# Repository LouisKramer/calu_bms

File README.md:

# calu_bms

Battery management system for a stationary high-voltage LFP home storage
(8 × 16S modules, expandable to 10, wireless slaves, master with CAN to the inverter).

Development follows the documents in [docs/](docs/):

1. [System requirements](docs/requirements.md) (draft, incl. configuration parameters)
2. [Slave requirements](docs/slave_requirements.md) (draft, hardware + software)
3. [Master requirements](docs/master_requirements.md) (draft, hardware + software), based on the
   [master concept review](docs/master_concept_review.md) of `hw/master/CALU_BMS_MASTER.epro2`
4. [Plausibility check](docs/plausibility_check.md) of the requirements
5. [System architecture](docs/system_architecture.md), [master architecture](docs/master_architecture.md), [slave architecture](docs/slave_architecture.md)
6. [Project plan](docs/plan.md) with work items ([tools/work_items.json](tools/work_items.json), GitHub issues via [tools/create_github_issues.py](tools/create_github_issues.py))

## Repository layout

| Folder | Content |
|---|---|
| [docs/](docs/) | requirements, plausibility check, architecture, plan, datasheets, test reports |
| [firmware/](firmware/) | MicroPython firmware: `common/`, `slave/`, `master/`, `build/` |
| [hw/](hw/) | hardware: `slave/`, `master/` |
| [tools/](tools/) | helper scripts (work items, later CAN sniffer, calibration, production test) |
| [tests/](tests/) | host tests (CPython + pytest) with simulated hardware |

## Development

```
pip install -r requirements-dev.txt
pytest
```

Work items are GitHub issues (milestones M0…M3). Each work item gets a branch (`w01-repo-skeleton`)
and a pull request that references the issue (`Closes #2`).

## Earlier work

The `playground` branch (formerly `main`) holds the first prototypes, firmware and hardware.
It is kept as a reference only, together with these branches:

| Branch | Content |
|---|---|
| `playground` | first master/slave firmware (MicroPython), EasyEDA hardware 1.2/1.3, tools, datasheets |
| `slave-hw-2.0.1.0` | firmware cleanup, drivers and bring-up for slave hardware 2.0.1.0 |
| `slave-hw-3.0.0.0` | flying-capacitor slave in KiCad/SKiDL, active balancer review |

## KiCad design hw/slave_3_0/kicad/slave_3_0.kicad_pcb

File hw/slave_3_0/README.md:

# Slave 3.0.0.0 hardware (KiCad 10 + SKiDL)

The circuit is written in Python (SKiDL). Everything in `kicad/` except the PCB layout is generated.

| File | Content |
|---|---|
| `common.py` | KiCad paths, part helpers, reference numbering (one hundred block per sheet), shared nets |
| `power.py`, `mcu.py`, `cells.py`, `meas_mux.py`, `adc.py`, `balancing.py` | one schematic sheet each |
| `slave_3_0.py` | top level: ERC, netlist, schematic, checks, `--pcb` |
| `sch_writer.py` | writes the KiCad schematic (symbols + global labels) and the project file, verifies it |
| `build_pcb.py` | creates the initial PCB (only if none exists) |
| `kicad/` | generated KiCad project: open `slave_3_0.kicad_pro` |

Specification and design reasoning: [../CALU_BMS_Slave_3_0_0_0_schematic.md](../CALU_BMS_Slave_3_0_0_0_schematic.md)

## Workflow

```
make hw_tools   # once: SKiDL into KiCad's Python
make sch        # edit *.py, then regenerate netlist + schematic (verified against the netlist)
make erc        # KiCad ERC
make pcb        # first time only: initial PCB with all footprints, nets and net classes
make drc        # KiCad DRC incl. schematic <-> PCB parity
```

After a circuit change: `make sch`, then in KiCad **reload the schematic** (schematic editor: File → Revert, or
close it), then in the PCB editor **Tools → Update PCB from Schematic (F8)** and save (Ctrl+S).
F8 uses the schematic editor's data in memory: without the reload it applies the old circuit.
Footprints stay linked to their symbols (deterministic UUIDs), so the layout is kept.

Do not edit the generated `.kicad_sch` files in KiCad; change the Python source instead.
The PCB (`slave_3_0.kicad_pcb`) is edited in KiCad as usual.

## Schematic style

No wires: every pin has a global label with its net name. Unnamed nets are called `N$<n>`.
`make sch` exports KiCad's netlist of the generated schematic and compares it pin by pin with the SKiDL
netlist, so the drawing can't differ from the circuit.

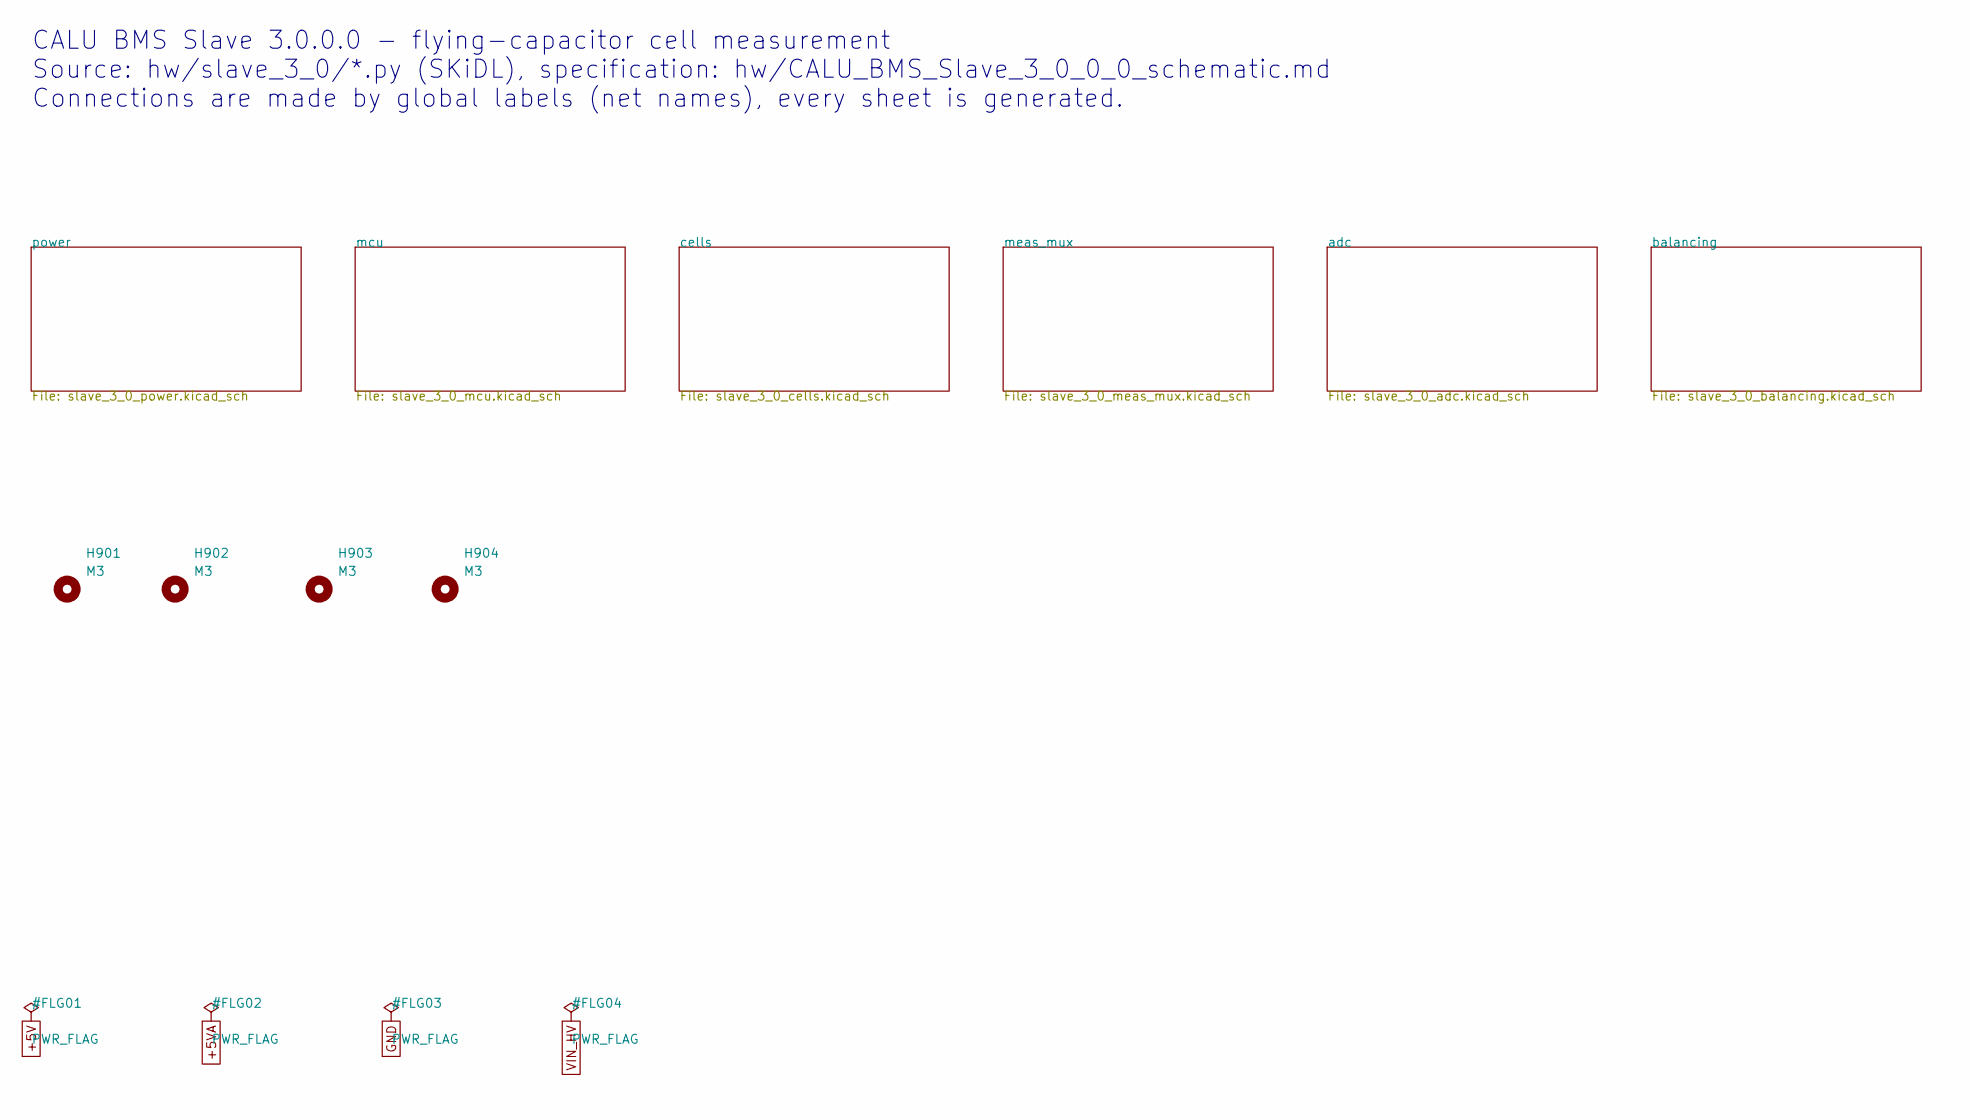
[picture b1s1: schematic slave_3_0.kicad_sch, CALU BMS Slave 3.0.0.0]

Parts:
H901, H902, H903, H904: M3; MountingHole_3.2mm_M3

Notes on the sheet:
CALU BMS Slave 3.0.0.0 - flying-capacitor cell measurement Source: hw/slave_3_0/*.py (SKiDL), specification: hw/CALU_BMS_Slave_3_0_0_0_schematic.md Connections are made by global labels (net names), every sheet is generated.

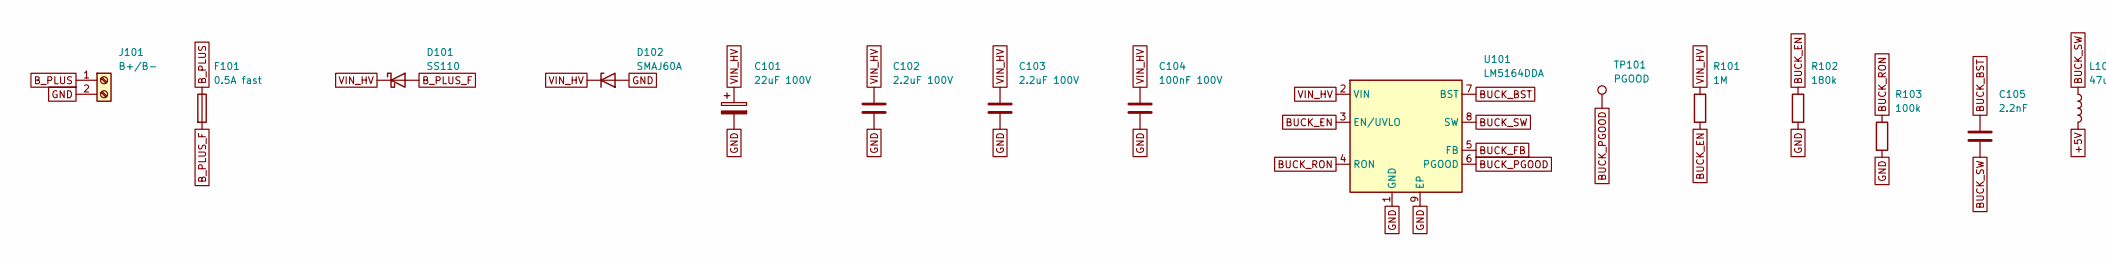
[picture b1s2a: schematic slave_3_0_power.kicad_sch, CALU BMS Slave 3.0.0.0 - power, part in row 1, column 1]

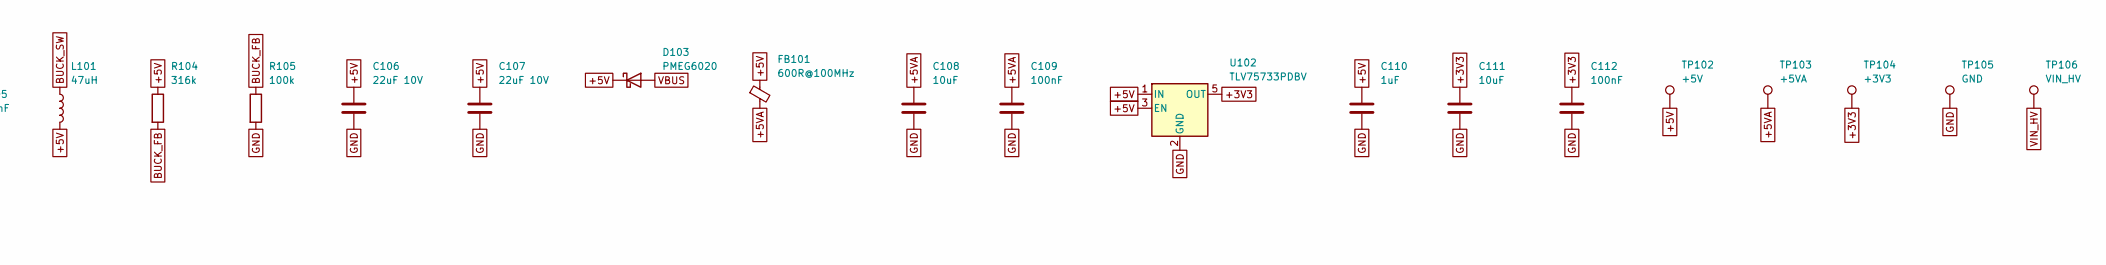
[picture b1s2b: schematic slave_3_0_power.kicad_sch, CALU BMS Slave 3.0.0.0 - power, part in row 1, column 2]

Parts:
C101: 22uF 100V; CP_Elec_8x10
C102, C103: 2.2uF 100V; C_1210_3225Metric
C104: 100nF 100V; C_0603_1608Metric
C105: 2.2nF; C_0603_1608Metric
C106, C107: 22uF 10V; C_1206_3216Metric
C108, C111: 10uF; C_0603_1608Metric
C109, C112: 100nF; C_0603_1608Metric
C110: 1uF; C_0603_1608Metric
D101: SS110; D_SMA
D102: SMAJ60A; D_SMA
D103: PMEG6020; D_SOD-123F
F101: 0.5A fast; Fuse_1206_3216Metric
FB101: 600R@100MHz; L_0603_1608Metric
J101: B+/B-; PhoenixContact_MSTBA_2,5_2-G-5,08_1x02_P5.08mm_Horizontal
L101: 47uH; L_Bourns_SRR1260
R101: 1M; R_0805_2012Metric
R102: 180k; R_0603_1608Metric
R103, R105: 100k; R_0603_1608Metric
R104: 316k; R_0603_1608Metric
TP101: PGOOD; TestPoint_Pad_D1.0mm
TP102: +5V; TestPoint_Pad_D1.0mm
TP103: +5VA; TestPoint_Pad_D1.0mm
TP104: +3V3; TestPoint_Pad_D1.0mm
TP105: GND; TestPoint_Pad_D1.0mm
TP106: VIN_HV; TestPoint_Pad_D1.0mm
U101: LM5164DDA; HSOP-8-1EP_3.9x4.9mm_P1.27mm_EP2.41x3.1mm_ThermalVias
U102: TLV75733PDBV; SOT-23-5

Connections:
+3V3: C111.1, C112.1, TP104.1 (1_1), U102.5 (OUT); also elsewhere on the board
+5V: C106.1, C107.1, C110.1, D103.1 (K), FB101.1, L101.2, R104.1, TP102.1 (1_1), U102.1 (IN), U102.3 (EN); also elsewhere on the board
+5VA: C108.1, C109.1, FB101.2, TP103.1 (1_1); also elsewhere on the board
BUCK_BST: C105.1, U101.7 (BST)
BUCK_EN: R101.2, R102.1, U101.3 (EN/UVLO)
BUCK_FB: R104.2, R105.1, U101.5 (FB)
BUCK_PGOOD: TP101.1 (1_1), U101.6 (PGOOD)
BUCK_RON: R103.1, U101.4 (RON)
BUCK_SW: C105.2, L101.1, U101.8 (SW)
B_PLUS: F101.1, J101.1
B_PLUS_F: D101.2 (A), F101.2
GND: C101.2, C102.2, C103.2, C104.2, C106.2, C107.2, C108.2, C109.2, C110.2, C111.2, C112.2, D102.2 (A), J101.2, R102.2, R103.2, R105.2, TP105.1 (1_1), U101.1 (GND), U101.9 (EP), U102.2 (GND); also elsewhere on the board
VBUS: D103.2 (A); also elsewhere on the board
VIN_HV: C101.1, C102.1, C103.1, C104.1, D101.1 (K), D102.1 (K), R101.1, TP106.1 (1_1), U101.2 (VIN)

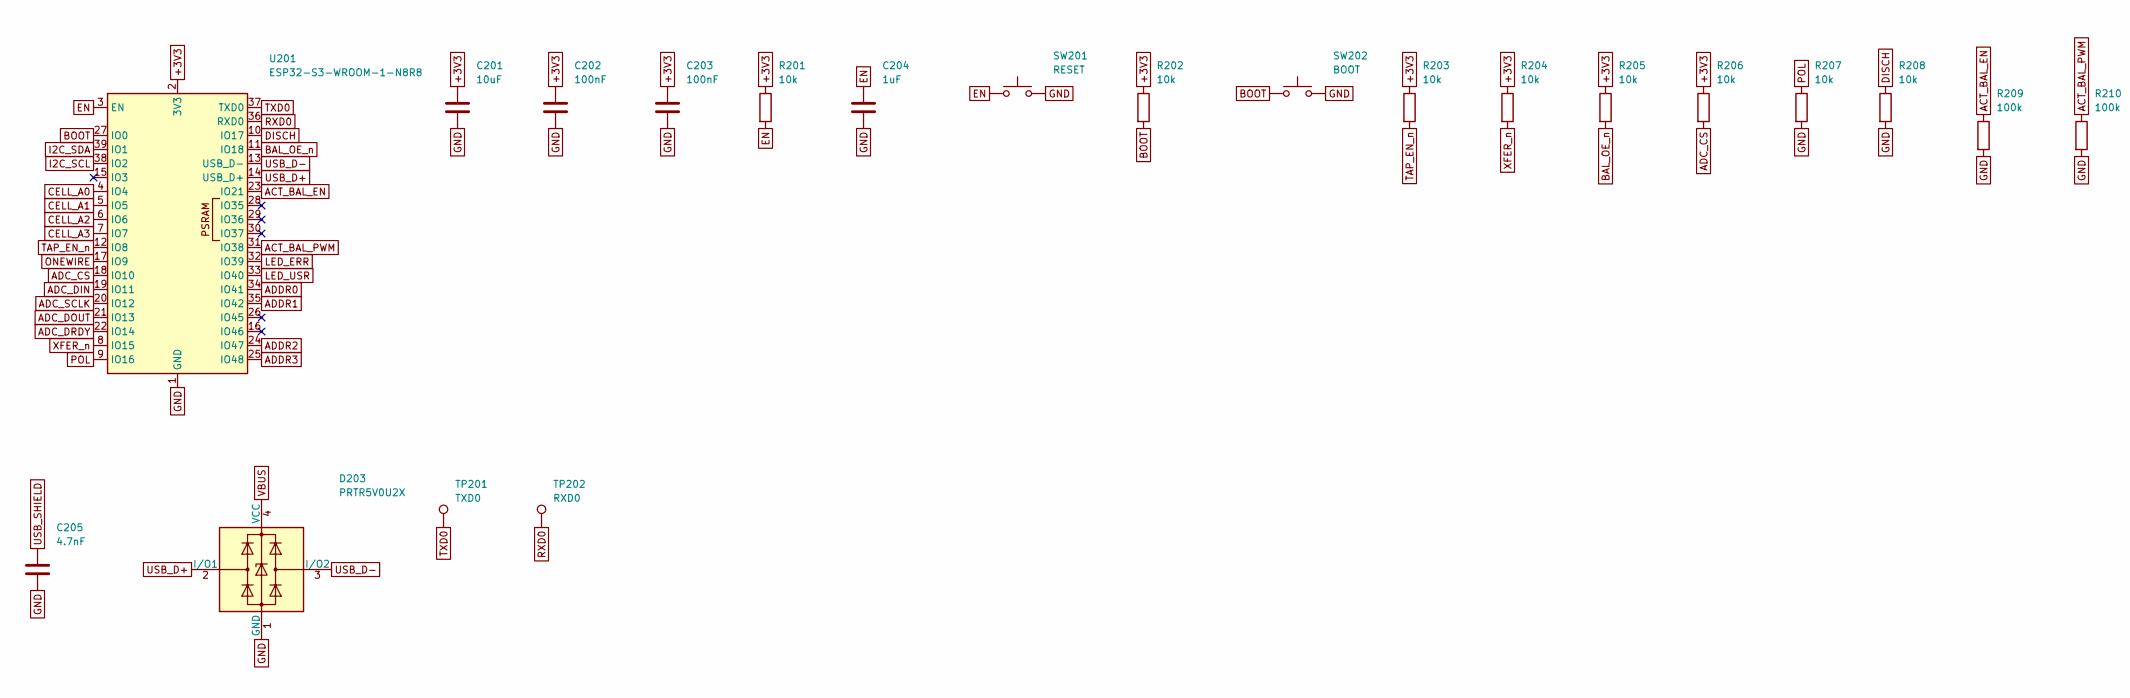
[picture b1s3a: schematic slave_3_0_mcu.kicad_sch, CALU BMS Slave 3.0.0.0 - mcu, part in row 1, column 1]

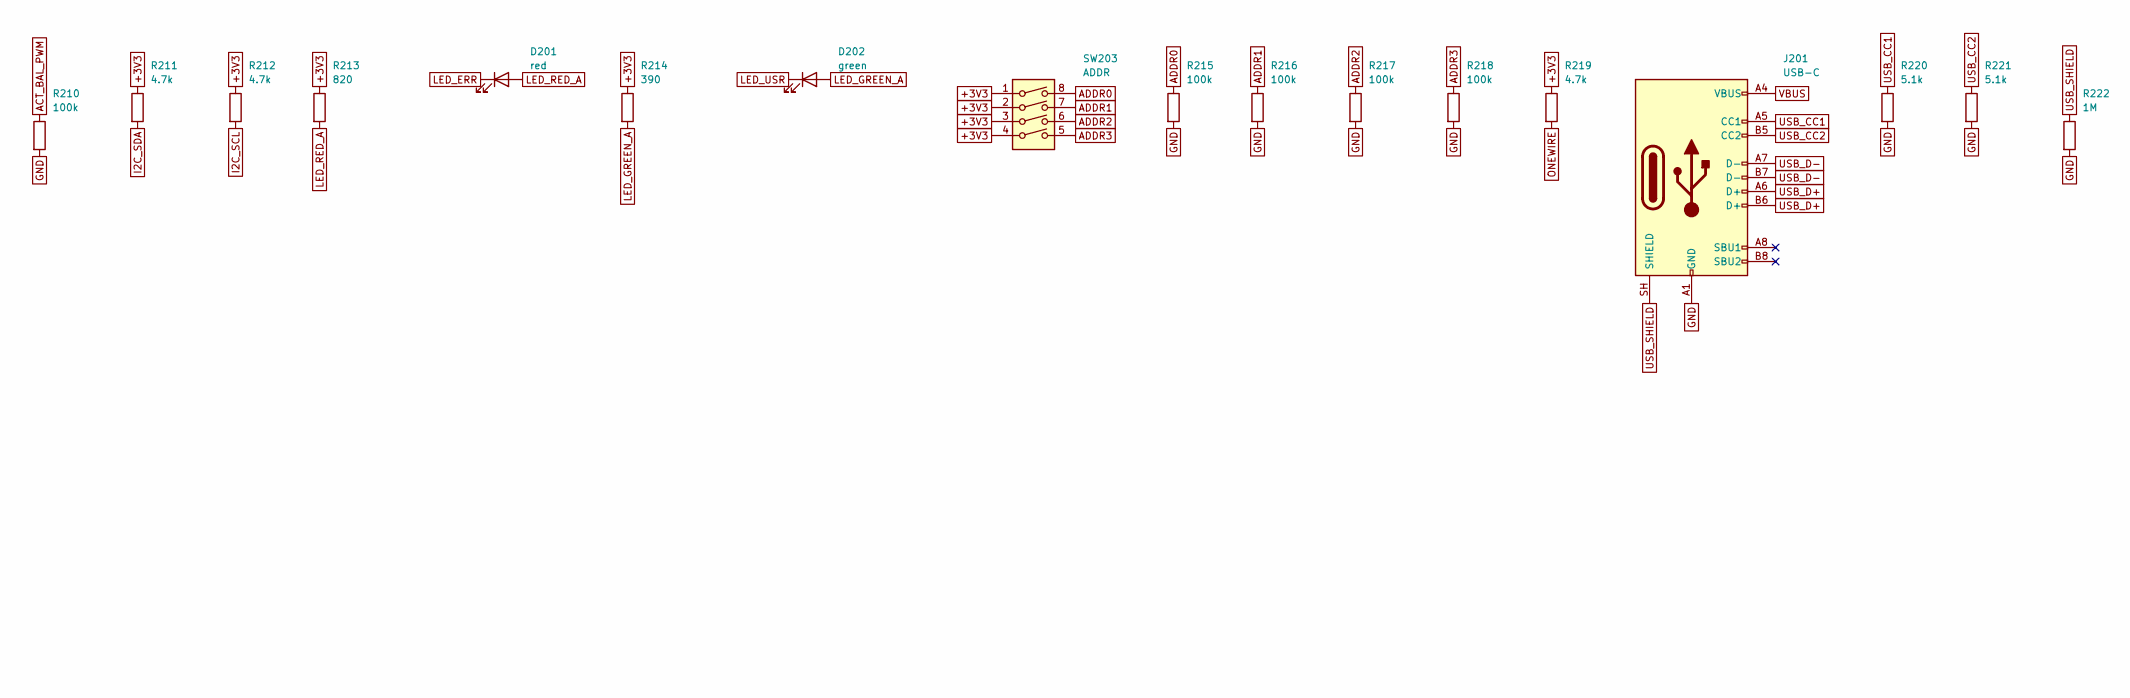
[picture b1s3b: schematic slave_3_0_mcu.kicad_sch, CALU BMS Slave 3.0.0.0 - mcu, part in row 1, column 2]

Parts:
C201: 10uF; C_0603_1608Metric
C202, C203: 100nF; C_0603_1608Metric
C204: 1uF; C_0603_1608Metric
C205: 4.7nF; C_0603_1608Metric
D201: red; LED_0603_1608Metric
D202: green; LED_0603_1608Metric
D203: PRTR5V0U2X; SOT-143
J201: USB-C; USB_C_Receptacle_HRO_TYPE-C-31-M-12
R201, R202, R203, R204, R205, R206, R207, R208: 10k; R_0603_1608Metric
R209, R210, R215, R216, R217, R218: 100k; R_0603_1608Metric
R211, R212, R219: 4.7k; R_0603_1608Metric
R213: 820; R_0603_1608Metric
R214: 390; R_0603_1608Metric
R220, R221: 5.1k; R_0603_1608Metric
R222: 1M; R_0603_1608Metric
SW201: RESET; SW_SPST_B3U-1000P
SW202: BOOT; SW_SPST_B3U-1000P
SW203: ADDR; SW_DIP_SPSTx04_Slide_9.78x12.34mm_W7.62mm_P2.54mm
TP201: TXD0; TestPoint_Pad_D1.0mm
TP202: RXD0; TestPoint_Pad_D1.0mm
U201: ESP32-S3-WROOM-1-N8R8; ESP32-S3-WROOM-1

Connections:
+3V3: C201.1, C202.1, C203.1, R201.1, R202.1, R203.1, R204.1, R205.1, R206.1, R211.1, R212.1, R213.1, R214.1, R219.1, SW203.1, SW203.2, SW203.3, SW203.4, U201.2 (3V3); also elsewhere on the board
ACT_BAL_EN: R209.1, U201.23 (IO21); also elsewhere on the board
ACT_BAL_PWM: R210.1, U201.31 (IO38); also elsewhere on the board
ADC_CS: R206.2, U201.18 (IO10); also elsewhere on the board
ADC_DIN: U201.19 (IO11); also elsewhere on the board
ADC_DOUT: U201.21 (IO13); also elsewhere on the board
ADC_DRDY: U201.22 (IO14); also elsewhere on the board
ADC_SCLK: U201.20 (IO12); also elsewhere on the board
ADDR0: R215.1, SW203.8, U201.34 (IO41)
ADDR1: R216.1, SW203.7, U201.35 (IO42)
ADDR2: R217.1, SW203.6, U201.24 (IO47)
ADDR3: R218.1, SW203.5, U201.25 (IO48)
BAL_OE_n: R205.2, U201.11 (IO18); also elsewhere on the board
BOOT: R202.2, SW202.1, U201.27 (IO0)
CELL_A0: U201.4 (IO4); also elsewhere on the board
CELL_A1: U201.5 (IO5); also elsewhere on the board
CELL_A2: U201.6 (IO6); also elsewhere on the board
CELL_A3: U201.7 (IO7); also elsewhere on the board
DISCH: R208.1, U201.10 (IO17); also elsewhere on the board
EN: C204.1, R201.2, SW201.1, U201.3 (EN)
GND: C201.2, C202.2, C203.2, C204.2, C205.2, D203.1 (GND), J201.A1 (GND), J201.A12 (GND), J201.B1 (GND), J201.B12 (GND), R207.2, R208.2, R209.2, R210.2, R215.2, R216.2, R217.2, R218.2, R220.2, R221.2, R222.2, SW201.2, SW202.2, U201.1 (GND), U201.40 (GND), U201.41 (GND); also elsewhere on the board
I2C_SCL: R212.2, U201.38 (IO2); also elsewhere on the board
I2C_SDA: R211.2, U201.39 (IO1); also elsewhere on the board
LED_ERR: D201.1 (K), U201.32 (IO39)
LED_GREEN_A: D202.2 (A), R214.2
LED_RED_A: D201.2 (A), R213.2
LED_USR: D202.1 (K), U201.33 (IO40)
ONEWIRE: R219.2, U201.17 (IO9); also elsewhere on the board
POL: R207.1, U201.9 (IO16); also elsewhere on the board
RXD0: TP202.1 (1_1), U201.36 (RXD0)
TAP_EN_n: R203.2, U201.12 (IO8); also elsewhere on the board
TXD0: TP201.1 (1_1), U201.37 (TXD0)
USB_CC1: J201.A5 (CC1), R220.1
USB_CC2: J201.B5 (CC2), R221.1
USB_D+: D203.2 (I/O1), J201.A6 (D+), J201.B6 (D+), U201.14 (USB_D+)
USB_D-: D203.3 (I/O2), J201.A7 (D-), J201.B7 (D-), U201.13 (USB_D-)
USB_SHIELD: C205.1, J201.SH (SHIELD), R222.1
VBUS: D203.4 (VCC), J201.A4 (VBUS), J201.A9 (VBUS), J201.B4 (VBUS), J201.B9 (VBUS); also elsewhere on the board
XFER_n: R204.2, U201.8 (IO15); also elsewhere on the board

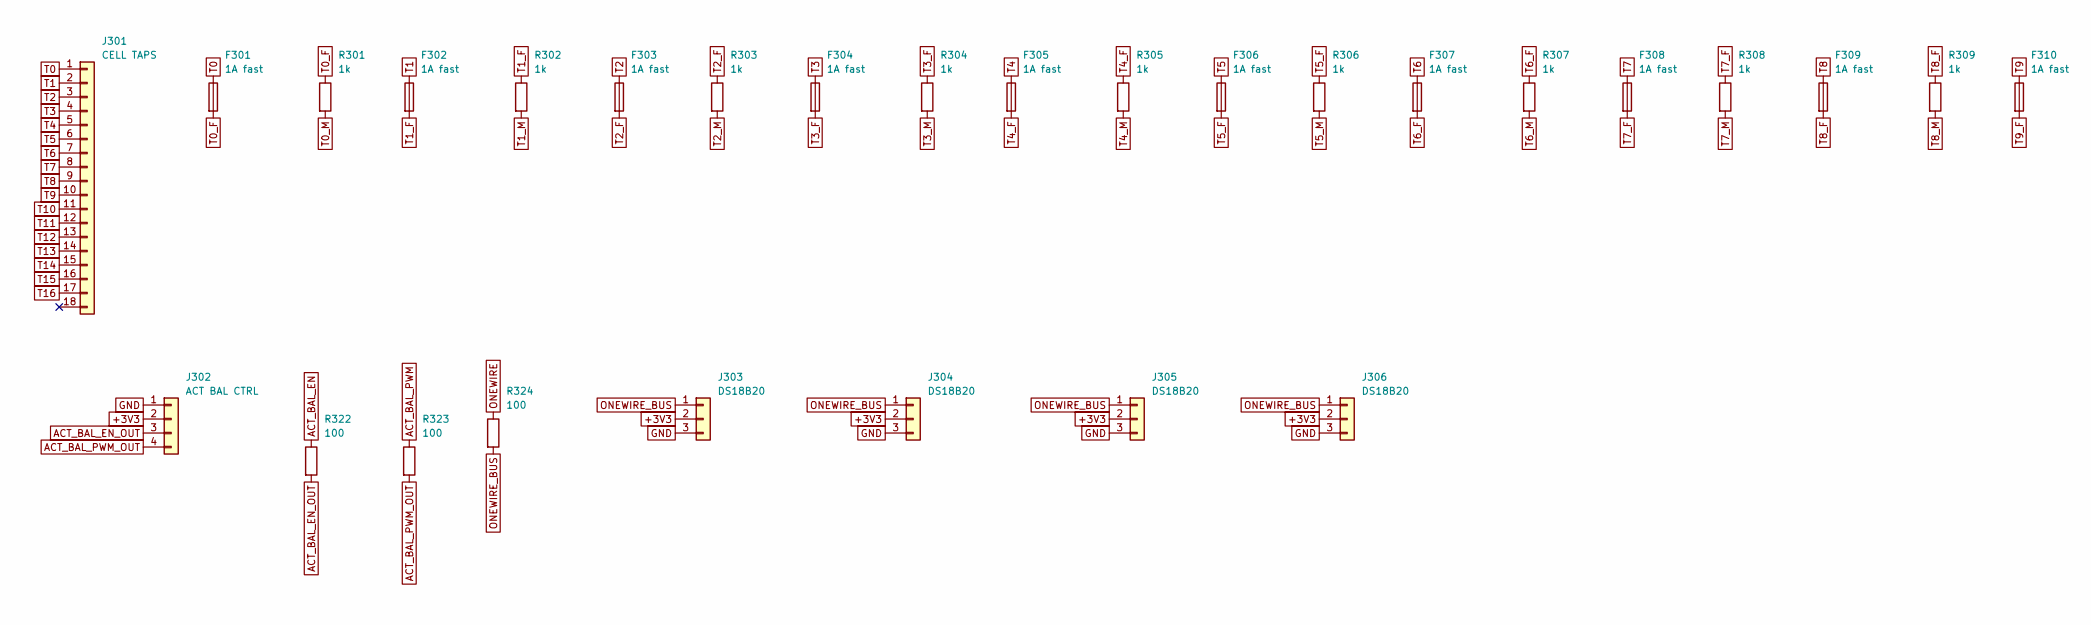
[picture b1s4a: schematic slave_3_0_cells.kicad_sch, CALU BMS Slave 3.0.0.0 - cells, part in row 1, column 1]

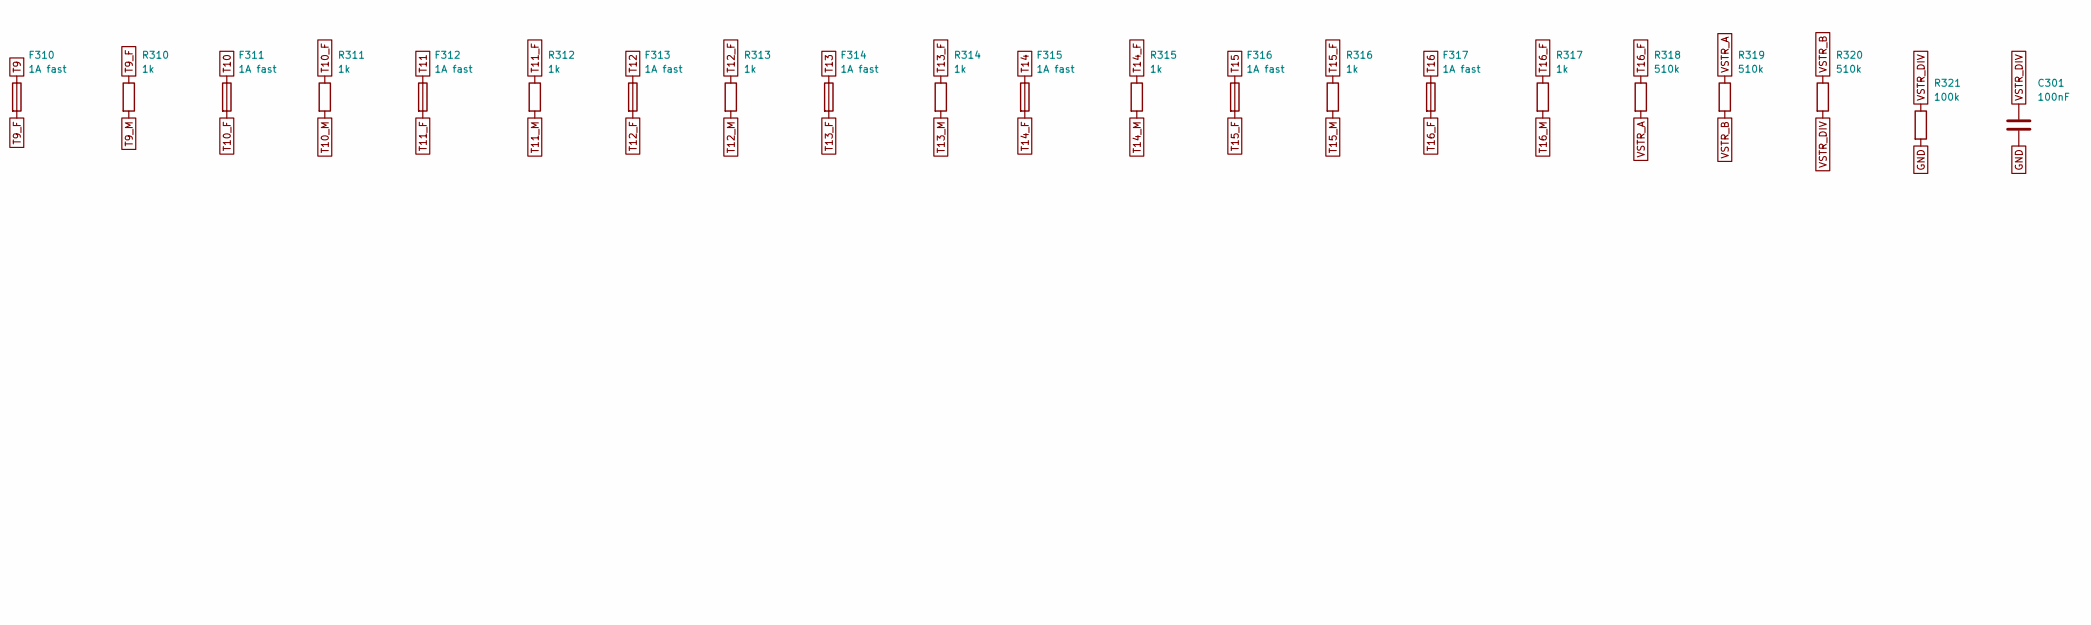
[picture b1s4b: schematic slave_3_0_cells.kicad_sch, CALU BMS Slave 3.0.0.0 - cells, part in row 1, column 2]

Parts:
C301: 100nF; C_0603_1608Metric
F301, F302, F303, F304, F305, F306, F307, F308, F309, F310, F311, F312, F313, F314, F315, F316, F317: 1A fast; Fuse_1206_3216Metric
J301: CELL TAPS; TerminalBlock_Degson_DG250-3.5-18P_1x18_P3.50mm_45Degree
J302: ACT BAL CTRL; JST_XH_B4B-XH-A_1x04_P2.50mm_Vertical
J303, J304, J305, J306: DS18B20; TerminalBlock_Degson_DG250-3.5-03P_1x03_P3.50mm_45Degree
R301, R302, R303, R304, R305, R306, R307, R308, R309, R310, R311, R312, R313, R314, R315, R316, R317: 1k; R_1206_3216Metric
R318, R319, R320: 510k; R_0805_2012Metric
R321: 100k; R_0603_1608Metric
R322, R323, R324: 100; R_0603_1608Metric

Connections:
+3V3: J302.2, J303.2, J304.2, J305.2, J306.2; also elsewhere on the board
ACT_BAL_EN: R322.1; also elsewhere on the board
ACT_BAL_EN_OUT: J302.3, R322.2
ACT_BAL_PWM: R323.1; also elsewhere on the board
ACT_BAL_PWM_OUT: J302.4, R323.2
GND: C301.2, J302.1, J303.3, J304.3, J305.3, J306.3, R321.2; also elsewhere on the board
ONEWIRE: R324.1; also elsewhere on the board
ONEWIRE_BUS: J303.1, J304.1, J305.1, J306.1, R324.2
T0: F301.1, J301.1
T0_F: F301.2, R301.1; also elsewhere on the board
T0_M: R301.2; also elsewhere on the board
T1: F302.1, J301.2
T1_F: F302.2, R302.1; also elsewhere on the board
T1_M: R302.2; also elsewhere on the board
T2: F303.1, J301.3
T2_F: F303.2, R303.1; also elsewhere on the board
T2_M: R303.2; also elsewhere on the board
T3: F304.1, J301.4
T3_F: F304.2, R304.1; also elsewhere on the board
T3_M: R304.2; also elsewhere on the board
T4: F305.1, J301.5
T4_F: F305.2, R305.1; also elsewhere on the board
T4_M: R305.2; also elsewhere on the board
T5: F306.1, J301.6
T5_F: F306.2, R306.1; also elsewhere on the board
T5_M: R306.2; also elsewhere on the board
T6: F307.1, J301.7
T6_F: F307.2, R307.1; also elsewhere on the board
T6_M: R307.2; also elsewhere on the board
T7: F308.1, J301.8
T7_F: F308.2, R308.1; also elsewhere on the board
T7_M: R308.2; also elsewhere on the board
T8: F309.1, J301.9
T8_F: F309.2, R309.1; also elsewhere on the board
T8_M: R309.2; also elsewhere on the board
T9: F310.1, J301.10
T9_F: F310.2, R310.1; also elsewhere on the board
T9_M: R310.2; also elsewhere on the board
T10: F311.1, J301.11
T10_F: F311.2, R311.1; also elsewhere on the board
T10_M: R311.2; also elsewhere on the board
T11: F312.1, J301.12
T11_F: F312.2, R312.1; also elsewhere on the board
T11_M: R312.2; also elsewhere on the board
T12: F313.1, J301.13
T12_F: F313.2, R313.1; also elsewhere on the board
T12_M: R313.2; also elsewhere on the board
T13: F314.1, J301.14
T13_F: F314.2, R314.1; also elsewhere on the board
T13_M: R314.2; also elsewhere on the board
T14: F315.1, J301.15
T14_F: F315.2, R315.1; also elsewhere on the board
T14_M: R315.2; also elsewhere on the board
T15: F316.1, J301.16
T15_F: F316.2, R316.1; also elsewhere on the board
T15_M: R316.2; also elsewhere on the board
T16: F317.1, J301.17
T16_F: F317.2, R317.1, R318.1; also elsewhere on the board
T16_M: R317.2; also elsewhere on the board
VSTR_A: R318.2, R319.1
VSTR_B: R319.2, R320.1
VSTR_DIV: C301.1, R320.2, R321.1; also elsewhere on the board

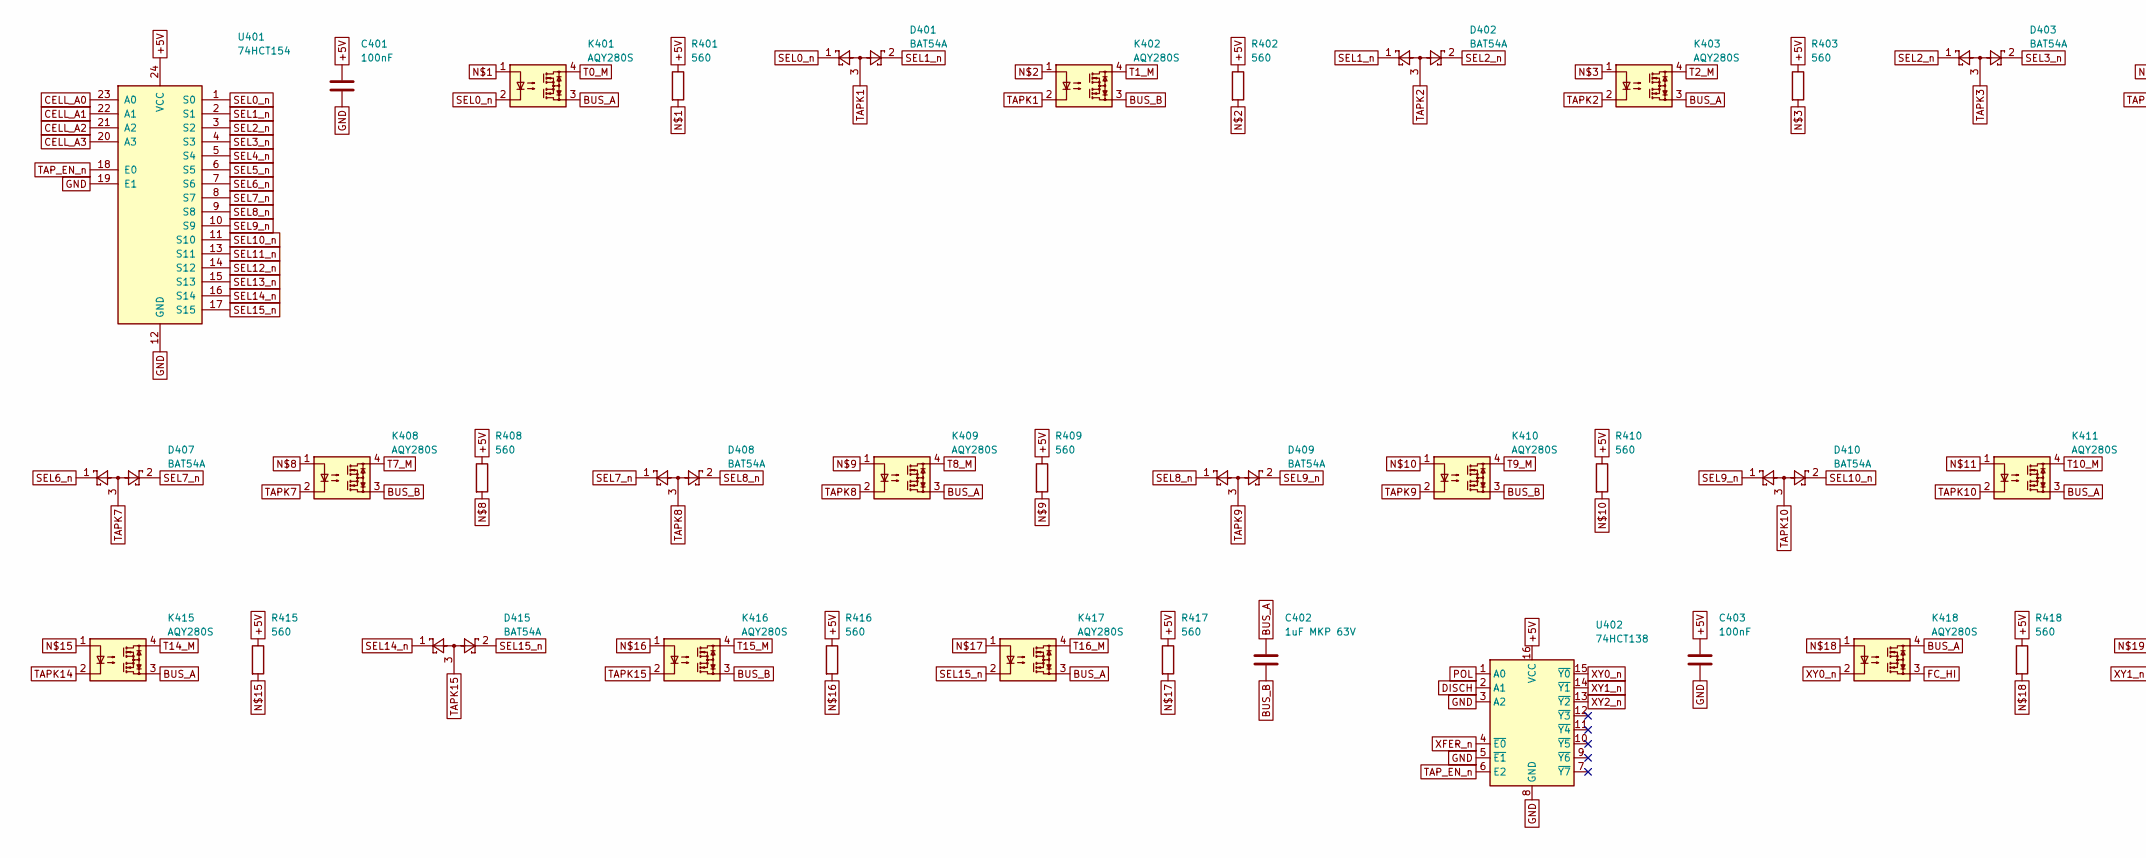
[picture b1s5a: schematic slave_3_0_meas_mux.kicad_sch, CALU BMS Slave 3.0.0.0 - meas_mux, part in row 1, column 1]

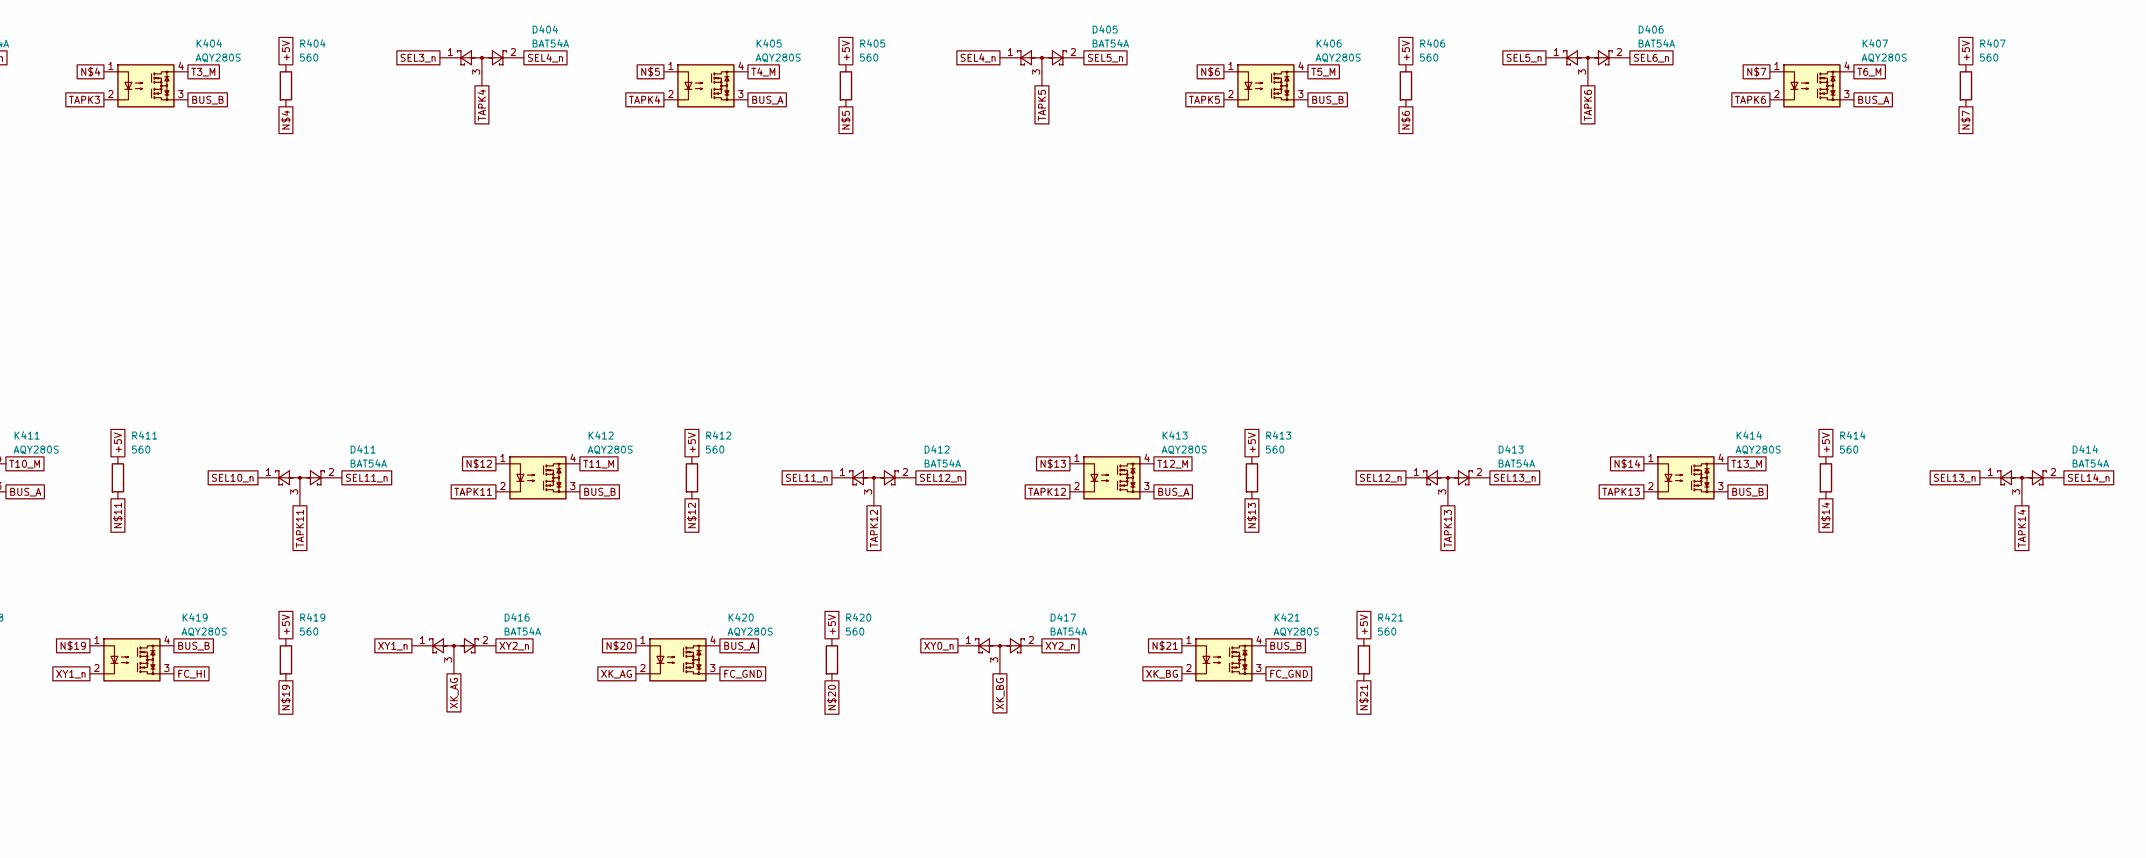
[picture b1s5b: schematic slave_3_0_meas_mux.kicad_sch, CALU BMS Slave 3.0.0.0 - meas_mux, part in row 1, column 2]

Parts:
C401, C403: 100nF; C_0603_1608Metric
C402: 1uF MKP 63V; C_Rect_L13.0mm_W5.0mm_P10.00mm_FKS3_FKP3_MKS4
D401, D402, D403, D404, D405, D406, D407, D408, D409, D410, D411, D412, D413, D414, D415, D416, D417: BAT54A; SOT-23
K401, K402, K403, K404, K405, K406, K407, K408, K409, K410, K411, K412, K413, K414, K415, K416, K417, K418, K419, K420, K421: AQY280S; SO-4_4.4x3.9mm_P2.54mm
R401, R402, R403, R404, R405, R406, R407, R408, R409, R410, R411, R412, R413, R414, R415, R416, R417, R418, R419, R420, R421: 560; R_0603_1608Metric
U401: 74HCT154; SOIC-24W_7.5x15.4mm_P1.27mm
U402: 74HCT138; SOIC-16_3.9x9.9mm_P1.27mm

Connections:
+5V: C401.1, C403.1, R401.1, R402.1, R403.1, R404.1, R405.1, R406.1, R407.1, R408.1, R409.1, R410.1, R411.1, R412.1, R413.1, R414.1, R415.1, R416.1, R417.1, R418.1, R419.1, R420.1, R421.1, U401.24 (VCC), U402.16 (VCC); also elsewhere on the board
BUS_A: C402.1, K401.3, K403.3, K405.3, K407.3, K409.3, K411.3, K413.3, K415.3, K417.3, K418.4, K420.4
BUS_B: C402.2, K402.3, K404.3, K406.3, K408.3, K410.3, K412.3, K414.3, K416.3, K419.4, K421.4
CELL_A0: U401.23 (A0); also elsewhere on the board
CELL_A1: U401.22 (A1); also elsewhere on the board
CELL_A2: U401.21 (A2); also elsewhere on the board
CELL_A3: U401.20 (A3); also elsewhere on the board
DISCH: U402.2 (A1); also elsewhere on the board
FC_GND: K420.3, K421.3; also elsewhere on the board
FC_HI: K418.3, K419.3; also elsewhere on the board
GND: C401.2, C403.2, U401.12 (GND), U401.19 (E1), U402.3 (A2), U402.5 (~E1), U402.8 (GND); also elsewhere on the board
unnamed: K401.1, R401.2
unnamed: K402.1, R402.2
unnamed: K403.1, R403.2
unnamed: K404.1, R404.2
unnamed: K405.1, R405.2
unnamed: K406.1, R406.2
unnamed: K407.1, R407.2
unnamed: K408.1, R408.2
unnamed: K409.1, R409.2
unnamed: K410.1, R410.2
unnamed: K411.1, R411.2
unnamed: K412.1, R412.2
unnamed: K413.1, R413.2
unnamed: K414.1, R414.2
unnamed: K415.1, R415.2
unnamed: K416.1, R416.2
unnamed: K417.1, R417.2
unnamed: K418.1, R418.2
unnamed: K419.1, R419.2
unnamed: K420.1, R420.2
unnamed: K421.1, R421.2
POL: U402.1 (A0); also elsewhere on the board
SEL0_n: D401.1, K401.2, U401.1 (S0)
SEL1_n: D401.2, D402.1, U401.2 (S1)
SEL2_n: D402.2, D403.1, U401.3 (S2)
SEL3_n: D403.2, D404.1, U401.4 (S3)
SEL4_n: D404.2, D405.1, U401.5 (S4)
SEL5_n: D405.2, D406.1, U401.6 (S5)
SEL6_n: D406.2, D407.1, U401.7 (S6)
SEL7_n: D407.2, D408.1, U401.8 (S7)
SEL8_n: D408.2, D409.1, U401.9 (S8)
SEL9_n: D409.2, D410.1, U401.10 (S9)
SEL10_n: D410.2, D411.1, U401.11 (S10)
SEL11_n: D411.2, D412.1, U401.13 (S11)
SEL12_n: D412.2, D413.1, U401.14 (S12)
SEL13_n: D413.2, D414.1, U401.15 (S13)
SEL14_n: D414.2, D415.1, U401.16 (S14)
SEL15_n: D415.2, K417.2, U401.17 (S15)
T0_M: K401.4; also elsewhere on the board
T1_M: K402.4; also elsewhere on the board
T2_M: K403.4; also elsewhere on the board
T3_M: K404.4; also elsewhere on the board
T4_M: K405.4; also elsewhere on the board
T5_M: K406.4; also elsewhere on the board
T6_M: K407.4; also elsewhere on the board
T7_M: K408.4; also elsewhere on the board
T8_M: K409.4; also elsewhere on the board
T9_M: K410.4; also elsewhere on the board
T10_M: K411.4; also elsewhere on the board
T11_M: K412.4; also elsewhere on the board
T12_M: K413.4; also elsewhere on the board
T13_M: K414.4; also elsewhere on the board
T14_M: K415.4; also elsewhere on the board
T15_M: K416.4; also elsewhere on the board
T16_M: K417.4; also elsewhere on the board
TAPK1: D401.3, K402.2
TAPK2: D402.3, K403.2
TAPK3: D403.3, K404.2
TAPK4: D404.3, K405.2
TAPK5: D405.3, K406.2
TAPK6: D406.3, K407.2
TAPK7: D407.3, K408.2
TAPK8: D408.3, K409.2
TAPK9: D409.3, K410.2
TAPK10: D410.3, K411.2
TAPK11: D411.3, K412.2
TAPK12: D412.3, K413.2
TAPK13: D413.3, K414.2
TAPK14: D414.3, K415.2
TAPK15: D415.3, K416.2
TAP_EN_n: U401.18 (E0), U402.6 (E2); also elsewhere on the board
XFER_n: U402.4 (~E0); also elsewhere on the board
XK_AG: D416.3, K420.2
XK_BG: D417.3, K421.2
XY0_n: D417.1, K418.2, U402.15 (~Y0)
XY1_n: D416.1, K419.2, U402.14 (~Y1)
XY2_n: D416.2, D417.2, U402.13 (~Y2)
